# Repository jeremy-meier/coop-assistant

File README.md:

# Coop Assistant
An ESPHome based automatic chicken coop door integrated with Home Assistant

The Coop Assistant project has the following features:
* Integrated DHT22 temperature and humidity sensor
* Integrated VEML7700 ambient light sensor to enable automatic open/close of coop door
* Two inputs for reed relay door sensors - I use these for the nesting box and larger door in our coop
* Motor drive output for controlling a smaller door ('chicken door') via a linear actuator
  * This is integrated with Home Assisstant using a Cover component.  The ADS1115 Analog to Digital converter senses current in each leg of the H-bridge drive to determine when the door is closed.
  * Home Assistant can be used to configure manual operation of the chicken door, or automatic mode can be used to determine the lighting level when the door should be opened or closed.
* Output for connecting a 12V LED strip for coop lighting
* Inputs for connecting switches for manual Open/Close/Stop operations

See https://github.com/jeremy-meier/coop-assistant for additional documentation.

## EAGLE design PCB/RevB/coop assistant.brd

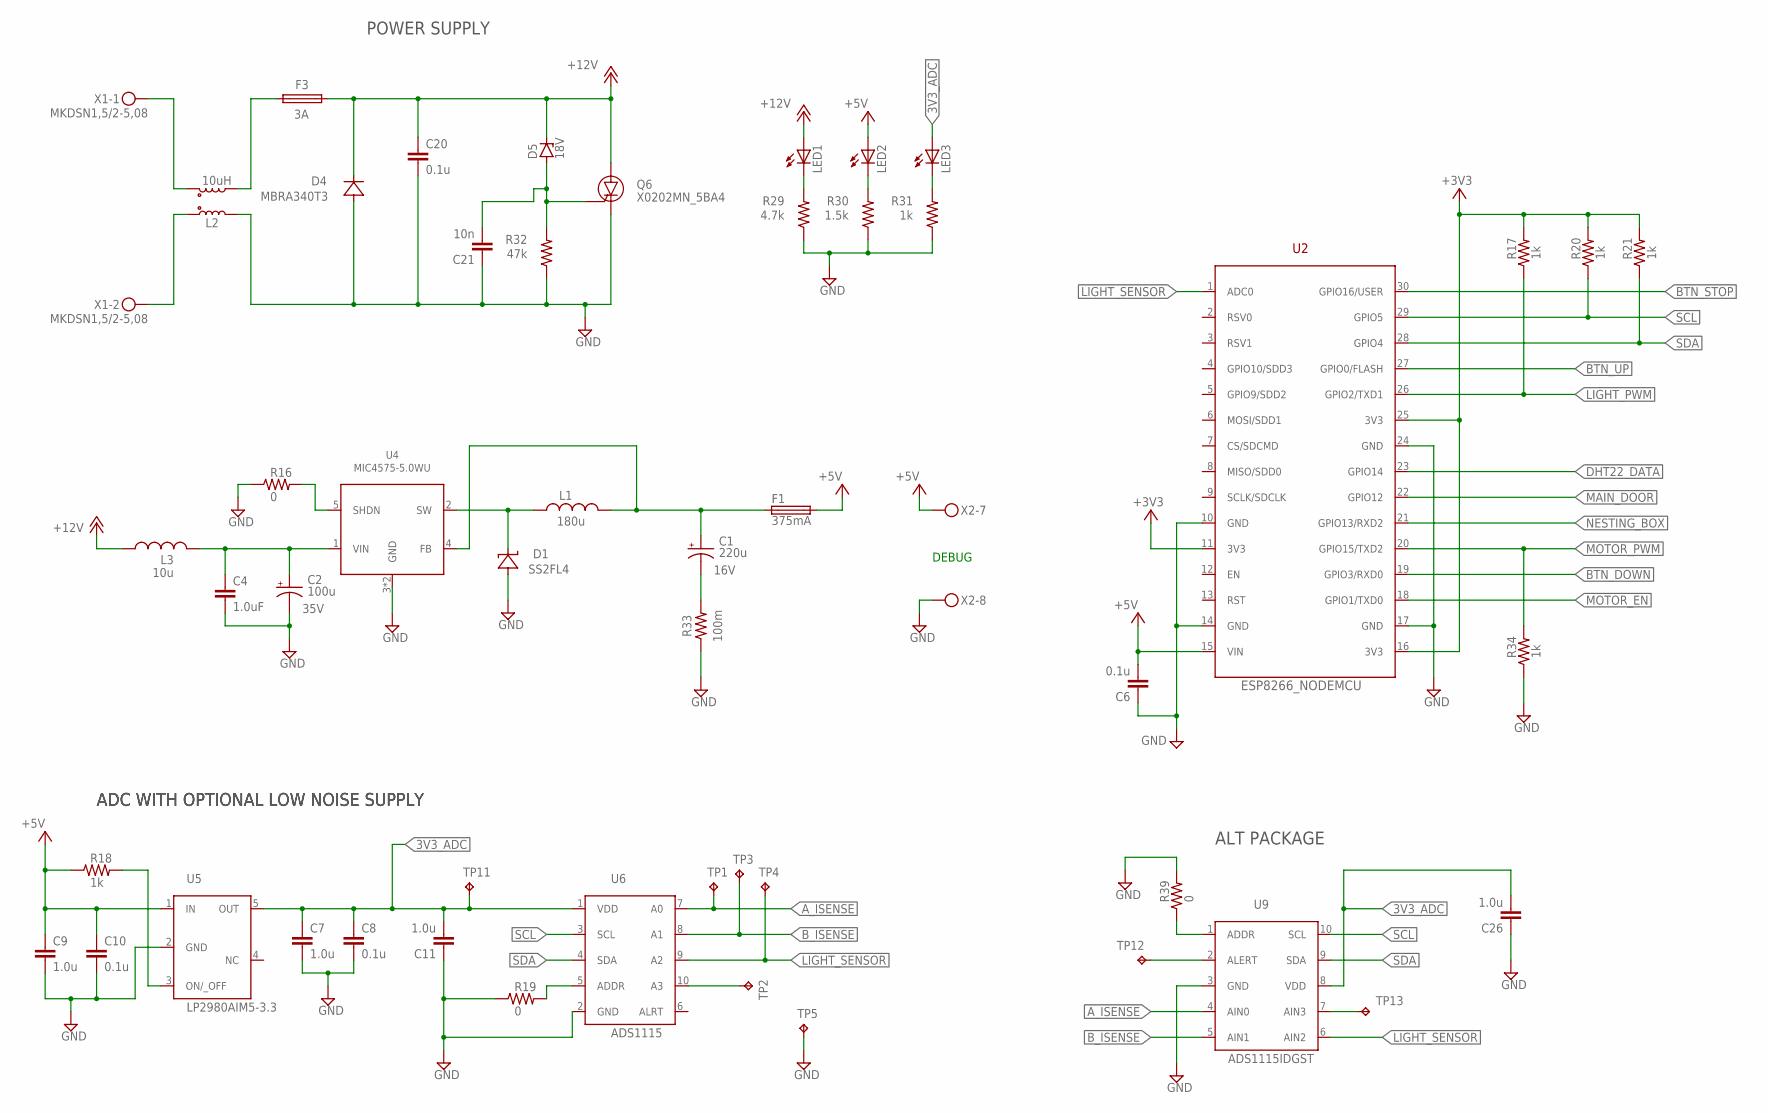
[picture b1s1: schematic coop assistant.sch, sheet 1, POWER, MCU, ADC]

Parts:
C1: 220u; CAPPRD250W50D630H800B; VOLTAGE 16V
C2: 100u; CAPPRD350W60D800H1200B; VOLTAGE 35V
C4: 1.0uF; 0805
C6, C8, C10: 0.1u; 0603
C7, C9, C11, C26: 1.0u; 0805
C20: 0.1u; C0805
C21: 10n; C0805
D1: SS2FL4; SMF
D4: MBRA340T3; SMA
D5: 18V; SOT23
F1: 375mA; 0603
F3: 3A; FUSM9750X381N
L1: 180u; INDM120120X780N
L2: 10uH; COILCRAFT_MSD1260
L3: 10u; INDM120120X780N
LED1, LED2, LED3: LEDCHIP-LED0805; CHIP-LED0805
Q6: X0202MN_5BA4; SOT-223
R16, R19, R39: 0; R0805
R17, R18, R20, R21, R31, R34: 1k; R0805
R29: 4.7k; R0805
R30: 1.5k; R0805
R32: 47k; R0805
R33: 100m; RESC3216X70
TP1, TP2, TP3, TP4, TP5, TP11, TP12, TP13: TPTP15SQ; TP15SQ
U2: ESP8266_NODEMCU; NODEMCUESP8266
U4: MIC4575-5.0WU; TO263-5
U5: LP2980AIM5-3.3; SOT23-5
U6: ADS1115; HDRV10W64P254_1X10_2800X508X838B
U9: ADS1115IDGST; 10VSSOP
X1: MKDSN1,5/2-5,08
X2: MKDSN1,5/8-5,08

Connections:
3V3_ADC: C7.1, C8.1, C11.2, C26.2, LED3.A, TP11.TP, U5.5 (OUT), U6.1 (VDD), U9.8 (VDD)
5VBUCK_SHDN: R16.2, U4.5 (SHDN)
5VBUCK_SW: D1.K (C), L1.1, U4.2 (SW)
5VBUCK_VIN: C2.POS (+), C4.1, L3.2, U4.1 (VIN)
5VBUCK_VOUT: C1.POS (+), F1.1, L1.2, U4.4 (FB)
5VBUCK_VOUT_ESR: C1.NEG (-), R33.2
+3V3: R17.2, R20.2, R21.2, U2.11 (3V3), U2.16 (3V3), U2.25 (3V3); also elsewhere on the board
+5V: C6.2, C9.1, C10.1, F1.2, LED2.A, R18.1, U2.15 (VIN), U5.1 (IN), X2.7
+12V: C20.1, D4.C, D5.3 (C), F3.2, L3.1, LED1.A, Q6.A, Q6.A1 (A); also elsewhere on the board
+12V_PREFUSE: F3.1, L2.3
ADS1115_ADDR: R19.2, U6.5 (ADDR)
A_ISENSE: TP1.TP, U6.7 (A0), U9.4 (AIN0); also elsewhere on the board
BTN_DOWN: U2.19 (GPIO3/RXD0); also elsewhere on the board
BTN_STOP: U2.30 (GPIO16/USER); also elsewhere on the board
BTN_UP: U2.27 (GPIO0/FLASH); also elsewhere on the board
B_ISENSE: TP3.TP, U6.8 (A1), U9.5 (AIN1); also elsewhere on the board
DHT22_DATA: U2.23 (GPIO14); also elsewhere on the board
GND: C2.NEG (-), C4.2, C6.1, C7.2, C8.2, C9.2, C10.2, C11.1, C20.2, C21.1, C26.1, D1.A, D4.A, L2.4, Q6.K, R16.1, R19.1, R29.1, R30.1, R31.1, R32.1, R33.1, R34.1, R39.2, TP5.TP, U2.10 (GND), U2.14 (GND), U2.17 (GND), U2.24 (GND), U4.3 (GND), U4.6 (GND), U5.2 (GND), U6.2 (GND), U9.3 (GND), X2.8; also elsewhere on the board
LED_3V3_ADC: LED3.C, R31.2
LED_5V: LED2.C, R30.2
LED_12V: LED1.C, R29.2
LIGHT_PWM: R17.1, U2.26 (GPIO2/TXD1); also elsewhere on the board
LIGHT_SENSOR: TP4.TP, U2.1 (ADC0), U6.9 (A2), U9.6 (AIN2); also elsewhere on the board
MAIN_DOOR: U2.22 (GPIO12); also elsewhere on the board
MOTOR_EN: U2.18 (GPIO1/TXD0); also elsewhere on the board
MOTOR_PWM: R34.2, U2.20 (GPIO15/TXD2); also elsewhere on the board
unnamed: TP2.TP, U6.10 (A3)
unnamed: TP12.TP, U9.2 (ALERT)
unnamed: R39.1, U9.1 (ADDR)
unnamed: TP13.TP, U9.7 (AIN3)
NESTING_BOX: U2.21 (GPIO13/RXD2); also elsewhere on the board
SCL: R20.1, U2.29 (GPIO5), U6.3 (SCL), U9.10 (SCL); also elsewhere on the board
SDA: R21.1, U2.28 (GPIO4), U6.4 (SDA), U9.9 (SDA); also elsewhere on the board
VADC_EN: R18.2, U5.3 (ON/_OFF)
VIN+: L2.1, X1.1
VIN-: L2.2, X1.2
VIN_CROWBAR_GATE: C21.2, D5.1 (A), Q6.G, R32.2

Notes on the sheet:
POWER SUPPLY
ADC WITH OPTIONAL LOW NOISE SUPPLY
DEBUG
ALT PACKAGE

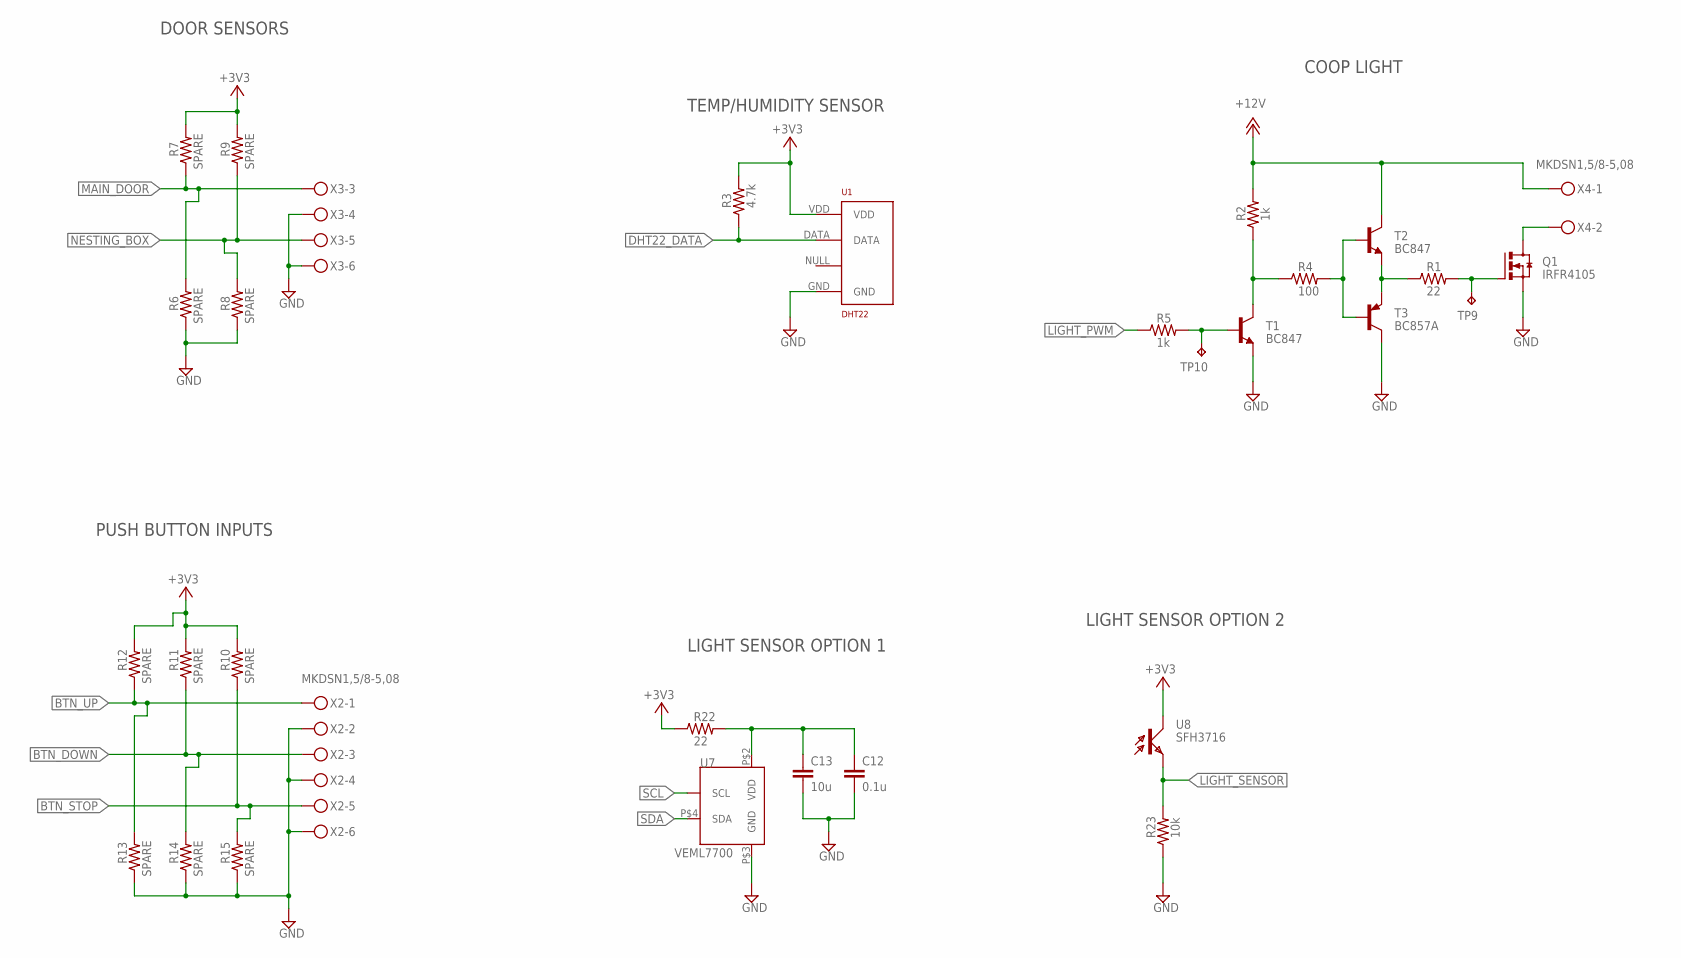
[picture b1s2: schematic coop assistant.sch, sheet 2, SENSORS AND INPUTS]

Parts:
C12: 0.1u; 0603
C13: 10u; 0805
Q1: IRFR4105; TO252
R1, R22: 22; R0805
R2, R5: 1k; R0805
R3: 4.7k; R0805
R4: 100; R0805
R6, R7, R8, R9, R10, R11, R12, R13, R14, R15: SPARE; R0805
R23: 10k; R0805
T1, T2: BC847; SOT23
T3: BC857A; SOT23-BEC
TP9, TP10: TPTP15SQ; TP15SQ
U1: DHT22; RHT03_DHT-22/RA
U7: VEML7700
U8: SFH3716; 0805
X2, X3, X4: MKDSN1,5/8-5,08

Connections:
+3V3: R3.2, R7.2, R9.2, R10.2, R11.2, R12.2, R22.1, U1.VDD, U8.1 (C); also elsewhere on the board
+12V: R2.2, T2.3 (C), X4.1; also elsewhere on the board
BTN_DOWN: R11.1, R14.2, X2.3; also elsewhere on the board
BTN_STOP: R10.1, R15.2, X2.5; also elsewhere on the board
BTN_UP: R12.1, R13.2, X2.1; also elsewhere on the board
DHT22_DATA: R3.1, U1.DATA; also elsewhere on the board
GND: C12.2, C13.2, Q1.2 (S), R6.1, R8.1, R13.1, R14.1, R15.1, R23.1, T1.2 (E), T3.C, U1.GND, U7.P$3 (GND), X2.2, X2.4, X2.6, X3.4, X3.6; also elsewhere on the board
LIGHT_GATE_PRERES: R1.1, T2.2 (E), T3.E
LIGHT_OUT: Q1.3 (D), X4.2
LIGHT_PWM: R5.1; also elsewhere on the board
LIGHT_PWM_BASE: R5.2, T1.1 (B), TP10.TP
LIGHT_PWM_EMITTER: R2.1, R4.1, T1.3 (C)
LIGHT_PWM_TOTEM: R4.2, T2.1 (B), T3.B
LIGHT_SENSOR: R23.2, U8.2 (E); also elsewhere on the board
LIGHT_SENSOR_VDD: C12.1, C13.1, R22.2, U7.P$2 (VDD)
LIGHT_VGATE: Q1.1 (G), R1.2, TP9.TP
MAIN_DOOR: R6.2, R7.1, X3.3; also elsewhere on the board
NESTING_BOX: R8.2, R9.1, X3.5; also elsewhere on the board
SCL: U7.P$1 (SCL); also elsewhere on the board
SDA: U7.P$4 (SDA); also elsewhere on the board

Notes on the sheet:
DOOR SENSORS
PUSH BUTTON INPUTS
TEMP/HUMIDITY SENSOR
LIGHT SENSOR OPTION 1
LIGHT SENSOR OPTION 2
COOP LIGHT

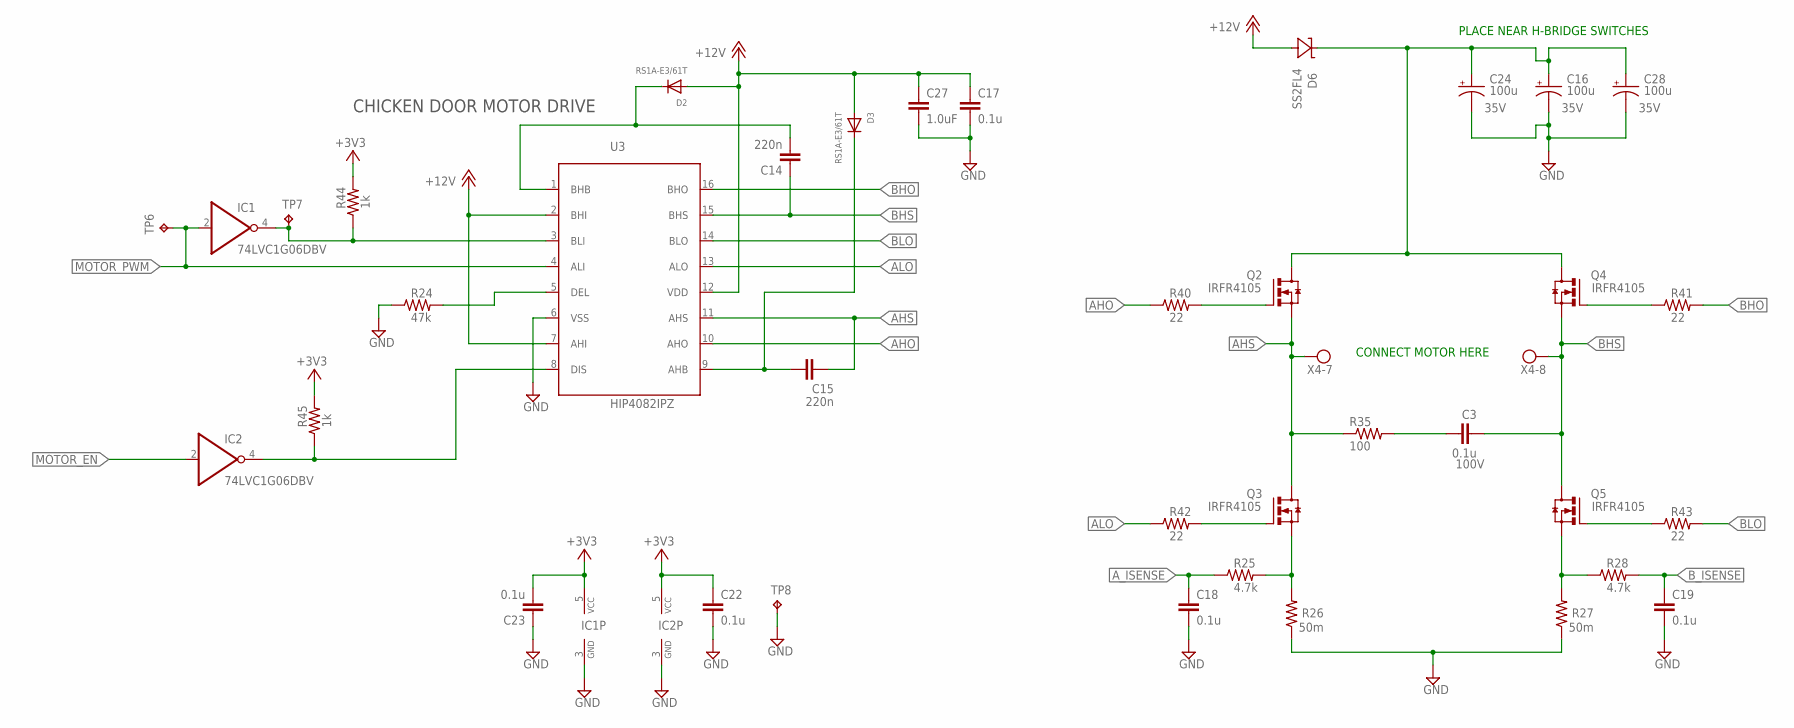
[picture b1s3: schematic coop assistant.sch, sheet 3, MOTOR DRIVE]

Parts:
C3: 0.1u; C0805; VOLTAGE 100V
C14, C15: 220n; 0805
C16, C24, C28: 100u; CAPPRD350W60D800H1200B; VOLTAGE 35V
C17, C18, C19, C22, C23: 0.1u; 0603
C27: 1.0uF; 0805
D2, D3: RS1A-E3/61T; SMADIODE
D6: SS2FL4; SMF
IC1, IC2: 74LVC1G06DBV; SOT23-5
Q2, Q3, Q4, Q5: IRFR4105; TO252
R24: 47k; R0805
R25, R28: 4.7k; R0805
R26, R27: 50m; R2512
R35: 100; R2512
R40, R41, R42, R43: 22; R0805
R44, R45: 1k; R0805
TP6, TP7, TP8: TPTP15SQ; TP15SQ
U3: HIP4082IPZ; DIP762W53P254L1969H508Q16B
X4: MKDSN1,5/8-5,08

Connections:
+3V3: C22.1, C23.2, IC1.5 (VCC), IC2.5 (VCC), R44.2, R45.2; also elsewhere on the board
+12V: C17.1, C27.1, D2.A, D3.A, D6.A, U3.2 (BHI), U3.7 (AHI), U3.12 (VDD); also elsewhere on the board
+12V_MOTOR: C16.POS (+), C24.POS (+), C28.POS (+), D6.K (C), Q2.3 (D), Q4.3 (D)
/MOTOR_EN: IC2.4 (O), R45.1, U3.8 (DIS)
/MOTOR_PWM: IC1.4 (O), R44.1, TP7.TP, U3.3 (BLI)
AHO: R40.1, U3.10 (AHO)
AHO_G: Q2.1 (G), R40.2
AHS: C15.2, Q2.2 (S), Q3.3 (D), R35.1, U3.11 (AHS), X4.7
ALO: R42.1, U3.13 (ALO)
ALO_G: Q3.1 (G), R42.2
ALS: Q3.2 (S), R25.2, R26.2
A_ISENSE: C18.1, R25.1; also elsewhere on the board
BHO: R41.2, U3.16 (BHO)
BHO_G: Q4.1 (G), R41.1
BHS: C3.2, C14.1, Q4.2 (S), Q5.3 (D), U3.15 (BHS), X4.8
BLO: R43.2, U3.14 (BLO)
BLO_G: Q5.1 (G), R43.1
BLS: Q5.2 (S), R27.2, R28.1
B_ISENSE: C19.1, R28.2; also elsewhere on the board
GND: C16.NEG (-), C17.2, C18.2, C19.2, C22.2, C23.1, C24.NEG (-), C27.2, C28.NEG (-), IC1.3 (GND), IC2.3 (GND), R24.1, R26.1, R27.1, TP8.TP, U3.6 (VSS); also elsewhere on the board
HIP4082_BOOTA: C15.1, D3.C, U3.9 (AHB)
HIP4082_BOOTB: C14.2, D2.C, U3.1 (BHB)
HIP4082_DLY: R24.2, U3.5 (DEL)
MOTOR_EN: IC2.2 (I); also elsewhere on the board
MOTOR_PWM: IC1.2 (I), TP6.TP, U3.4 (ALI); also elsewhere on the board
MOTOR_SNUB_RC: C3.1, R35.2

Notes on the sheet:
CHICKEN DOOR MOTOR DRIVE
PLACE NEAR H-BRIDGE SWITCHES
CONNECT MOTOR HERE

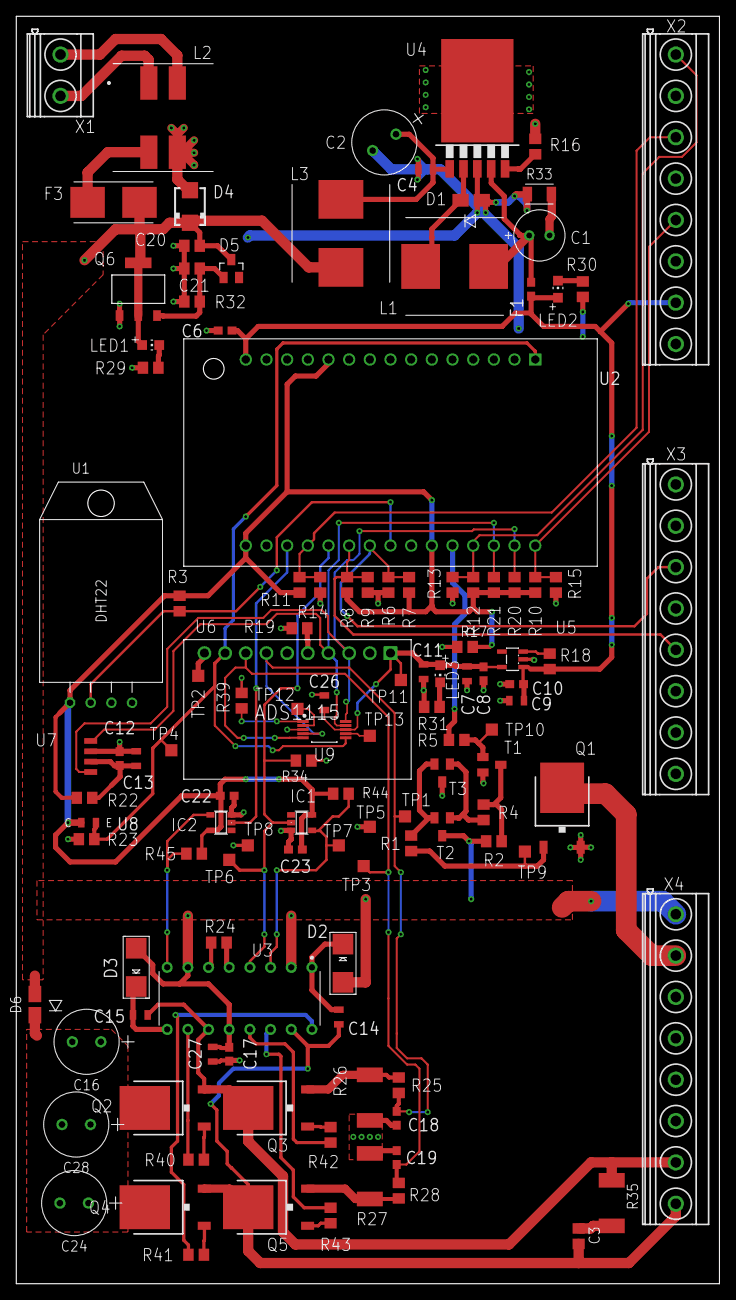
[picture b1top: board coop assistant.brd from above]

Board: 2 copper layers, 86.4 x 155.7 mm, 119 parts (0 on the bottom side), 63 nets.

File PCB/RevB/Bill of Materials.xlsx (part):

Part | Value | Device | Package | Description | CATEGORY | CREATED_BY | DIGIKEY_PARTNO | MANUFACTURER | MPN | OPERATING_TEMP | PACKAGE | PART_STATUS | POPULARITY | PROD_ID | RATING | ROHS_COMPLIANT | SERIES | SPICEPREFIX | SUB-CATEGORY | THERMALLOSS | TOLERANCE | TP_SIGNAL_NAME | TYPE | VALUE | VOLTAGE
C1 | 220u | CPOLRAD6.3X8 | CAPPRD250W50D630H800B | Radial Solid Polymer Aluminum Capacitors |  |  |  |  |  |  |  |  |  |  |  |  |  |  |  |  |  |  |  |  | 16V
C2 | 100u | CPOLRAD8X12 | CAPPRD350W60D800H1200B | Kemet Radial Solid Polymer Aluminum Capacitors |  |  |  |  |  |  |  |  |  |  |  |  |  |  |  |  |  |  |  |  | 35V
C3 | 0.1u | ﻿C-EUC0805 |  | 0.1uF 100V Ceramic
C4 | 1.0uF | 1.0UF-0805-25V-10% | 805 | 1¬µF ceramic capacitors |  |  |  |  |  |  |  |  |  | CAP-08064 |  |  |  |  |  |  |  |  |  | 1.0uF
C6 | 0.1u | 1.0UF-0603-16V-10% | 603 | 1¬µF ceramic capacitors |  |  |  |  |  |  |  |  |  | CAP-00868 |  |  |  |  |  |  |  |  |  | 1.0uF
C7 | 1.0u | 1.0UF-0805-25V-10% | 805 | 1¬µF ceramic capacitors |  |  |  |  |  |  |  |  |  | CAP-08064 |  |  |  |  |  |  |  |  |  | 1.0uF
C8 | 0.1u | 1.0UF-0603-16V-10% | 603 | 1¬µF ceramic capacitors |  |  |  |  |  |  |  |  |  | CAP-00868 |  |  |  |  |  |  |  |  |  | 1.0uF
C9 | 1.0u | 1.0UF-0805-25V-10% | 805 | 1¬µF ceramic capacitors |  |  |  |  |  |  |  |  |  | CAP-08064 |  |  |  |  |  |  |  |  |  | 1.0uF
C10 | 0.1u | 1.0UF-0603-16V-10% | 603 | 1¬µF ceramic capacitors |  |  |  |  |  |  |  |  |  | CAP-00868 |  |  |  |  |  |  |  |  |  | 1.0uF
C11 | 1.0u | 1.0UF-0805-25V-10% | 805 | 1¬µF ceramic capacitors |  |  |  |  |  |  |  |  |  | CAP-08064 |  |  |  |  |  |  |  |  |  | 1.0uF
C12 | 0.1u | 1.0UF-0603-16V-10% | 603 | 1¬µF ceramic capacitors |  |  |  |  |  |  |  |  |  | CAP-00868 |  |  |  |  |  |  |  |  |  | 1.0uF
C13 | 10u | 1.0UF-0805-25V-(+80/-20%) | 805 | 1¬µF ceramic capacitors |  |  |  |  |  |  |  |  |  | CAP-11625 |  |  |  |  |  |  |  |  |  | 1.0uF
C14 | 220n | 1.0UF-0805-25V-(+80/-20%) | 805 | 1¬µF ceramic capacitors |  |  |  |  |  |  |  |  |  | CAP-11625 |  |  |  |  |  |  |  |  |  | 1.0uF
C15 | 220n | 1.0UF-0805-25V-(+80/-20%) | 805 | 1¬µF ceramic capacitors |  |  |  |  |  |  |  |  |  | CAP-11625 |  |  |  |  |  |  |  |  |  | 1.0uF
C16 | 100u | CPOLRAD8X12 | CAPPRD350W60D800H1200B | Kemet Radial Solid Polymer Aluminum Capacitors |  |  |  |  |  |  |  |  |  |  |  |  |  |  |  |  |  |  |  |  | 35V
C17 | 0.1u | 1.0UF-0603-16V-10% | 603 | 1¬µF ceramic capacitors |  |  |  |  |  |  |  |  |  | CAP-00868 |  |  |  |  |  |  |  |  |  | 1.0uF
C18 | 0.1u | 1.0UF-0603-16V-10% | 603 | 1¬µF ceramic capacitors |  |  |  |  |  |  |  |  |  | CAP-00868 |  |  |  |  |  |  |  |  |  | 1.0uF
C19 | 0.1u | 1.0UF-0603-16V-10% | 603 | 1¬µF ceramic capacitors |  |  |  |  |  |  |  |  |  | CAP-00868 |  |  |  |  |  |  |  |  |  | 1.0uF
C20 | 0.1u | C-EUC0805 | C0805 | CAPACITOR, European symbol |  |  |  |  |  |  |  |  | 88 |  |  |  |  | C
C21 | 10n | C-EUC0805 | C0805 | CAPACITOR, European symbol |  |  |  |  |  |  |  |  | 88 |  |  |  |  | C
C22 | 0.1u | 1.0UF-0603-16V-10% | 603 | 1¬µF ceramic capacitors |  |  |  |  |  |  |  |  |  | CAP-00868 |  |  |  |  |  |  |  |  |  | 1.0uF
C23 | 0.1u | 1.0UF-0603-16V-10% | 603 | 1¬µF ceramic capacitors |  |  |  |  |  |  |  |  |  | CAP-00868 |  |  |  |  |  |  |  |  |  | 1.0uF
C24 | 100u | CPOLRAD8X12 | CAPPRD350W60D800H1200B | Kemet Radial Solid Polymer Aluminum Capacitors |  |  |  |  |  |  |  |  |  |  |  |  |  |  |  |  |  |  |  |  | 35V
C26 | 1.0u | 1.0UF-0805-25V-10% | 805 | 1¬µF ceramic capacitors |  |  |  |  |  |  |  |  |  | CAP-08064 |  |  |  |  |  |  |  |  |  | 1.0uF
C27 | 1.0uF | 1.0UF-0805-25V-10% | 805 | 1¬µF ceramic capacitors |  |  |  |  |  |  |  |  |  | CAP-08064 |  |  |  |  |  |  |  |  |  | 1.0uF
C28 | 100u | CPOLRAD8X12 | CAPPRD350W60D800H1200B | Kemet Radial Solid Polymer Aluminum Capacitors |  |  |  |  |  |  |  |  |  |  |  |  |  |  |  |  |  |  |  |  | 35V
D1 | SS2FL4 | SS2FL4 | SMF | SCHOTTKY DIODE, 40V/2A
D2 | RS1A-E3/61T | DIODESMA | SMADIODE | Diode
D3 | RS1A-E3/61T | DIODESMA | SMADIODE | Diode
D4 | MBRA340T3 | MBRA340T3 | SMA | Surface Mount Schottky Power Rectifier |  |  |  |  |  |  |  |  | 9
D5 | 18V | ZENER-DIODESOT23 | SOT23 | Z-Diode |  |  |  |  |  |  |  |  | 3
F1 | 375mA | 494SERIESFUSE | 603
F3 | 3A | 154_OMNIBLOKF154 | FUSM9750X381N
IC1 | 74LVC1G06DBV | 74LVC1G06DBV | SOT23-5 | Single Inverter Buffer/Driver With Open-Drain Output |  |  |  |  |  |  |  |  | 0
IC2 | 74LVC1G06DBV | 74LVC1G06DBV | SOT23-5 | Single Inverter Buffer/Driver With Open-Drain Output |  |  |  |  |  |  |  |  | 0
L1 | 180u | MSS1278 | INDM120120X780N | SMT Power Inductors
L2 | 10uH | COILCRAFT_MSD1260 | COILCRAFT_MSD1260 | Shielded Coupled Inductors
L3 | 10u | MSS1278 | INDM120120X780N | SMT Power Inductors
LED1 |  | LEDCHIP-LED0805 | CHIP-LED0805 | LED
LED2 |  | LEDCHIP-LED0805 | CHIP-LED0805 | LED
LED3 |  | LEDCHIP-LED0805 | CHIP-LED0805 | LED
Q1 | IRFR4105 | IRFR4105 | TO252 | MOSFET 55V 1 N-CH HEXFET 45mOhms 22.7nC
Q2 | IRFR4105 | IRFR4105 | TO252 | MOSFET 55V 1 N-CH HEXFET 45mOhms 22.7nC
Q3 | IRFR4105 | IRFR4105 | TO252 | MOSFET 55V 1 N-CH HEXFET 45mOhms 22.7nC
Q4 | IRFR4105 | IRFR4105 | TO252 | MOSFET 55V 1 N-CH HEXFET 45mOhms 22.7nC
Q5 | IRFR4105 | IRFR4105 | TO252 | MOSFET 55V 1 N-CH HEXFET 45mOhms 22.7nC
Q6 | X0202MN_5BA4 | X0202MN_5BA4 | SOT-223 | SCR 600V 1.25A SOT-223
R1 | 22 | R-US_R0805 | R0805 | RESISTOR, American symbol
R2 | 1k | R-US_R0805 | R0805 | RESISTOR, American symbol
R3 | 4.7k | R-US_R0805 | R0805 | RESISTOR, American symbol
R4 | 100 | R-US_R0805 | R0805 | RESISTOR, American symbol
R5 | 1k | R-US_R0805 | R0805 | RESISTOR, American symbol
R16 | 0 | R-US_R0805 | R0805 | RESISTOR, American symbol
R17 | 1k | R-US_R0805 | R0805 | RESISTOR, American symbol
R18 | 1k | R-US_R0805 | R0805 | RESISTOR, American symbol
R19 | 0 | R-US_R0805 | R0805 | RESISTOR, American symbol
R20 | 1k | R-US_R0805 | R0805 | RESISTOR, American symbol
R21 | 1k | R-US_R0805 | R0805 | RESISTOR, American symbol
R22 | 22 | R-US_R0805 | R0805 | RESISTOR, American symbol
R23 | 10k | R-US_R0805 | R0805 | RESISTOR, American symbol
R24 | 47k | R-US_R0805 | R0805 | RESISTOR, American symbol
R25 | 4.7k | R-US_R0805 | R0805 | RESISTOR, American symbol
R26 | 50m | R-US_R2512 | R2512 | RESISTOR, American symbol
R27 | 50m | R-US_R2512 | R2512 | RESISTOR, American symbol
R28 | 4.7k | R-US_R0805 | R0805 | RESISTOR, American symbol
R29 | 4.7k | R-US_R0805 | R0805 | RESISTOR, American symbol
R30 | 1.5k | R-US_R0805 | R0805 | RESISTOR, American symbol
R31 | 1k | R-US_R0805 | R0805 | RESISTOR, American symbol
R32 | 47k | R-US_R0805 | R0805 | RESISTOR, American symbol
R33 | 100m | R-US_CHIP-1206(3216-METRIC) | RESC3216X70 | Resistor Fixed - ANSI | Resistor |  |  |  |  |  |  |  |  |  |  |  |  |  | Fixed
R34 | 1k | R-US_R0805 | R0805 | RESISTOR, American symbol
R35 | 100 | ﻿R-US_R2512 | R2512 | RESISTOR, American symbol
R39 | 0 | R-US_R0805 | R0805 | RESISTOR, American symbol
R40 | 22 | R-US_R0805 | R0805 | RESISTOR, American symbol
R41 | 22 | R-US_R0805 | R0805 | RESISTOR, American symbol
R42 | 22 | R-US_R0805 | R0805 | RESISTOR, American symbol
R43 | 22 | R-US_R0805 | R0805 | RESISTOR, American symbol
R44 | 1k | R-US_R0805 | R0805 | RESISTOR, American symbol
R45 | 1k | R-US_R0805 | R0805 | RESISTOR, American symbol
T1 | BC847 | BC847 | SOT23 | NPN TRANSISTOR |  |  |  |  |  |  |  |  | 5
T2 | BC847 | BC847 | SOT23 | NPN TRANSISTOR |  |  |  |  |  |  |  |  | 5
T3 | BC857A | BC857A | SOT23-BEC | 65 V, 100 mA PNP general-purpose transistor
TP1 | TPTP15SQ | TPTP15SQ | TP15SQ | Test pad |  |  |  |  |  |  |  |  | 0
TP2 | TPTP15SQ | TPTP15SQ | TP15SQ | Test pad |  |  |  |  |  |  |  |  | 0
TP3 | TPTP15SQ | TPTP15SQ | TP15SQ | Test pad |  |  |  |  |  |  |  |  | 0
TP4 | TPTP15SQ | TPTP15SQ | TP15SQ | Test pad |  |  |  |  |  |  |  |  | 0
TP5 | TPTP15SQ | TPTP15SQ | TP15SQ | Test pad |  |  |  |  |  |  |  |  | 0
TP6 | TPTP15SQ | TPTP15SQ | TP15SQ | Test pad |  |  |  |  |  |  |  |  | 0
TP7 | TPTP15SQ | TPTP15SQ | TP15SQ | Test pad |  |  |  |  |  |  |  |  | 0
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
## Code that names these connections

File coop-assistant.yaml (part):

# D0/GPIO16 - Push Button Stop
# D1/GPIO5  - I2C SCL
# D2/GPIO4  - I2C SDA
# D3/GPIO0  - Push Button Up
# D4/GPIO2  - Coop Light PWM
# D5/GPIO14 - DHT Sensor
# D6/GPIO12 - Main Door
# D7/GPIO13 - Nesting Box Lid
# D8/GPIO15 - Motor PWM
# RX/GPIO3  - Push Button Down
# TX/GPIO1  - Motor Drive Enable

esphome:
  name: coop-assistant
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captive_portal:

i2c:
  sda: GPIO4
  scl: GPIO5
  scan: false
  
ads1115:
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    
  - platform: gpio
    pin:
      number: GPIO12
      mode:
        input: true
        pullup: true
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    
  - platform: gpio
    pin:
      number: GPIO13
      mode:
        input: true
        pullup: true
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
  - platform: gpio
    pin:
      number: GPIO16
      mode:
        input: true
    id: button_stop
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    
  - platform: gpio
    pin:
      number: GPIO0
      inverted: true
      mode:
        input: true
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    
  - platform: gpio
    pin:
      number: GPIO3
      inverted: true
      mode:
        input: true
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
sensor:
  - platform: dht
    pin: GPIO14
    model: DHT22_TYPE2
    temperature:
      name: "Coop Temperature"
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      
output:
  - platform: esp8266_pwm
    pin: GPIO2
    frequency: 100 Hz
    inverted: true
    id: light_pwm

  - platform: esp8266_pwm
    pin: 
      number: GPIO15
      mode:
        output: true
    frequency: 10000 Hz
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    
  - platform: gpio
    pin:
      number: GPIO1
      mode: 
        output: true
    id: motor_drive_enable
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
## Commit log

2022-01-13 Adding Rev A PCB files and datasheets
2022-01-13 Update to readme
2022-02-02 Update ESPHome config with custom component for illuminance sensor
2022-02-03 Add main config yaml file
2022-02-12 Update with some improvements to illuminance sensor
2022-02-12 Better support for publishing events for automatic door
2022-02-13 Add feature list to README
2022-02-13 Adding Rev B PCB files
2022-08-24 Rev B PCB Update
2025-05-26 VEML7000 is now supported by esphome core

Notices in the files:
parts and their libraries:
SparkFun-Capacitors: Licensing: Creative Commons ShareAlike 4.0 International - https://creativecommons.org/licenses/by-sa/4.0
